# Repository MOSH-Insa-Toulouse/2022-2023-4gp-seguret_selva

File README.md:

# 2022-2023-4gp-seguret_selva
## Notre projet MOSH - julien &amp; clément  
  
Dans le cadre de l'UF "Du capteur au banc de test en Open Source Hardware", nous avons été amenés à réaliser un capteur de déformation low-tech à base de graphite
Le fonctionnement de ce capteur est basé sur la variation de résistance engendrée par la déformation de celui-ci.
La physique derrière cette variation de résistance vient du déplacement des électrons par effet tunnel entre les nanoparticules de graphite.
Après avoir appliqué une contrainte mécanique, la distance entre les nanoparticules varie, entraînant donc une modification de la conductivité du graphite.
Cela induit donc une variation de résistance du capteur.  
  
Voici une image représentant notre capteur low-tech à base de graphite :  

Dans ce fichier nous allons décrire tous les procédés qui ont permis d'aboutir à la création de ce capteur.  
  
Table des matières :  
  
* [1. Cahier des charges](#PremiereSection)  
* [2. Simulation électronique du circuit transimpédance sur LTSpice](#DeuxiemeSection) 
* [3. Le design de notre PCB sur KiCAD](#TroisiemeSection)
* [4. Notre code Arduino](#QuatriemeSection)  
* [5. Notre application Bluetooth](#CinquiemeSection)
* [6. Le banc de test et l'élaboration de la Datasheet](#SixiemeSection)  
    
### *1. Cahier des charges* 
  
Nous sommes en binôme pour réaliser ce projet qui comprend plusieurs différents livrables :  
* Un Shield PCB au préalable designé sur KiCAD  
* Une application Android fonctionnant par Bluetooth permettant de visualiser l'évolution de la résistance du capteur en temps réel  
* Un code Arduino permettant de calculer en temps réel la variation de résistance du capteur ainsi que de contrôler les élements du PCB  
* Une datasheet regroupant les caractéristiques de fonctionnement du capteur  
  
Ainsi, afin de réaliser ce projet, il nous a été nécessaire de réaliser la simulation du capteur sur le logiciel LTSpice pour avoir une idée de l'ordre de grandeur de la résitance de celui-ci. 
Nous avons ensuite utlisé le logiciel KiCAD dans le but de designer le Shield PCB relatif au bon fonctionnement du capteur, et redigé un code Arduino
permettant le contrôle de certains éléments du Shield tels que le Flex Sensor, le module Bluetooth et l'écran OLED. Ce code Arduino nous permet également de calculer 
en temps réel la valeur de la résistance du capteur.
Après avoir effectué tout cela, nous avons créé une application APK Android permettant de connecter le module Bluetooth du PCB au téléphone de Julien, et de
visualiser l'évolution de la résistance du capteur sur un graphique en temps réel.
Enfin, la dernière étape visait à la réalisation d'une datasheet, via la caractérisation de notre jauge de contrainte.  
  
Le matériel suivant a été nécessaire à la confection de notre projet :  
* Une carte Arduino UNO    
* Un module Bluetooth HC-05  
* Un écran OLED I2C  
* Un amplificateur opérationnel LTC1050  
* Deux résistances de 100 KOhms  
* Une résistance de 10 KOhms  
* Deux résistances de 1 KOhm  
* Deux condensateurs de 100 nF  
* Un condensateur de 100 µF  
* Une feuille de papier  
* Cinq crayons à papier différents  
  
### *2. Simulation électronique du circuit transimpédance sur LTSpice*  
  
Comme nous l'avons démontré dans le document nommé [Rapport LTSpice](https://github.com/MOSH-Insa-Toulouse/2022-2023-4gp-seguret_selva/blob/main/LTSpice/Rapport%20LTSpice.pdf), le capteur ne délivrait qu'une intensité très faible (de l'ordre de quelques nF). Aussi, la carte Arduino n'est capable de sortir qu'une tension entre 0 et 5V.  
Ainsi, il nous est apparu comme nécessaire de réaliser un circuit transimpédance afin de convertir les variations de courant du capteur en variations de tension, de sorte
que la carte Arduino puisse la lire en temps réel. En parallèle de tout ça, sur ce circuit, nous avons placé quelques filtres passe-bas nous permettant de réduire les bruits
liés à la mesure, et nous permettant à l'aide d'un amplificateur LTC1050 d'amplifier le signal de sortie.  
  
Voici, la simulation de notre amplificateur transimpédance réalisé sur le logiciel LTSpice :  

### *3. L'utilisation de KiCAD en vue de la création de notre PCB*   
  
Dans l'objectif de réaliser notre PCB, nous avons dû utiliser le logiciel KiCAD. Certains composants n'étant pas disponibles dans les librairies du logiciel, 
nous les avons créés afin de pouvoir designer tous les éléments dont nous avions besoin pour réaliser le Shield. Ce sont les éléments suivants accompagnés
de leur empreinte et de leur schéma :  
  
* Le module Bluetooth HC-05 :  
  
* L'amplificateur opérationnel LTC1050 :   
  
* L'écran OLED I2C :  
  
* Le Flex Sensor :  
   
* Le capteur graphite :  

Vous pouvez également visualiser ici le schéma de notre Shield Arduino ainsi que de la PCB :  

### *4. Notre code Arduino*   
  
Notre code Arduino nous a permis de connecter tous les éléments du Shield entre eux afin d'assurer le bon fonctionnement de celui-ci.  
Rappelons que notre code Arduino que l'on peut retrouver dans le document nommé [AffichageRes](https://github.com/MOSH-Insa-Toulouse/2022-2023-4gp-seguret_selva/blob/main/Code%20Arduino/AffichageRes) prend en charge les fonctionnalités suivantes :  
* L'envoi et la réception de données sur l'application APK via le module Bluetooth HC-05  
* Le calcul en temps réel de la variation de résistance associée à la déformation du capteur graphite  
* L'acquistion et l'affichage de cette valeur de résistance sur l'écran OLED  
* Le lancement de l'acquisition de données pour une certaine valeur de déformation du Flex Sensor  

### *5. Notre application Bluetooth*  
  
Notre application Andoid a été développée à l'aide du logiciel *MIT App Inventor*. Nous avons créé une interface graphique téléchargeable sur Android afin de :  
* Connecter une téléphone au PCB via le module Bluetooth  
* Visualiser en temps réel sous forme de graphique l'évolution de la résistance en fonction de la déformation  
* Afficher la résistance du capteur en temps réel  
  
### *6. Le banc de test et l'élaboration de la Datasheet*   
  
Comme nous avons créé un capteur graphite low-tech, nous avons également décidé d'utiliser un banc de test low-tech.
Le banc de test que vous pouvez voir ci-dessous a été créé il y a quelques années par l'un des professeurs de l'INSA Toulouse.  

Ce banc de test nous a permis de tester différents angles de courbure pour notre capteur. En effet, nous avons placé notre capteur graphite sur les différentes
portions de cette pièce, afin de faire varier sa résistance, que ce soit en tension ou en compression.
  
L’objectif de ce banc de test est de déterminer la variation relative de résistance de notre capteur en fonction de la déformation appliquée. Le capteur graphite est quant à lui scotché par une extrémité sur une autre feuille rigide, et pincé au niveau des pins de l’autre extrémité. L’objectif est de courber la feuille de papier rigide sur laquelle est scotché le capteur, afin que celui-ci adopte la forme des cercles de différents rayons.

L'ensemble de ces tests ont été réalisés pour 5 types de crayons différents. Les résultats et analyses de ceux-ci sont disponibles sur le document suivant nommé :
[Datasheet jauge](https://github.com/MOSH-Insa-Toulouse/2022-2023-4gp-seguret_selva/blob/main/Datasheet/Datasheet%20jauge.pdf)  
  
Il faut noter que notre capteur fonctionne assez bien car, pour n'importe quel type de crayon, la variation relative de résistance de notre capteur en fonction de la 
déformation appliquée est quasi-linéaire.  
  
Malheureusement, il est notable que notre capteur graphite s'endommage assez rapidement lorsque l'on le plie car le papier n'est pas solide. Il n'est donc pas
possible de réaliser la mesure plusieurs fois afin de vérifier ses résultats, ce qui rend la datasheet assez imprécise. Cela se traduit également par le fait que 
les courbes obtenues ne sont pas totalement linéaires. Aussi, le dépôt de graphite lors du coloriage du papier est assez aléatoire, rendant le capteur
encore plus imprécis.  
  
Tous ces éléments nous laissent ainsi penser que ce capteur low-tech est réalisable, mais n'est pas nécessairement très adapté à un usage industriel.

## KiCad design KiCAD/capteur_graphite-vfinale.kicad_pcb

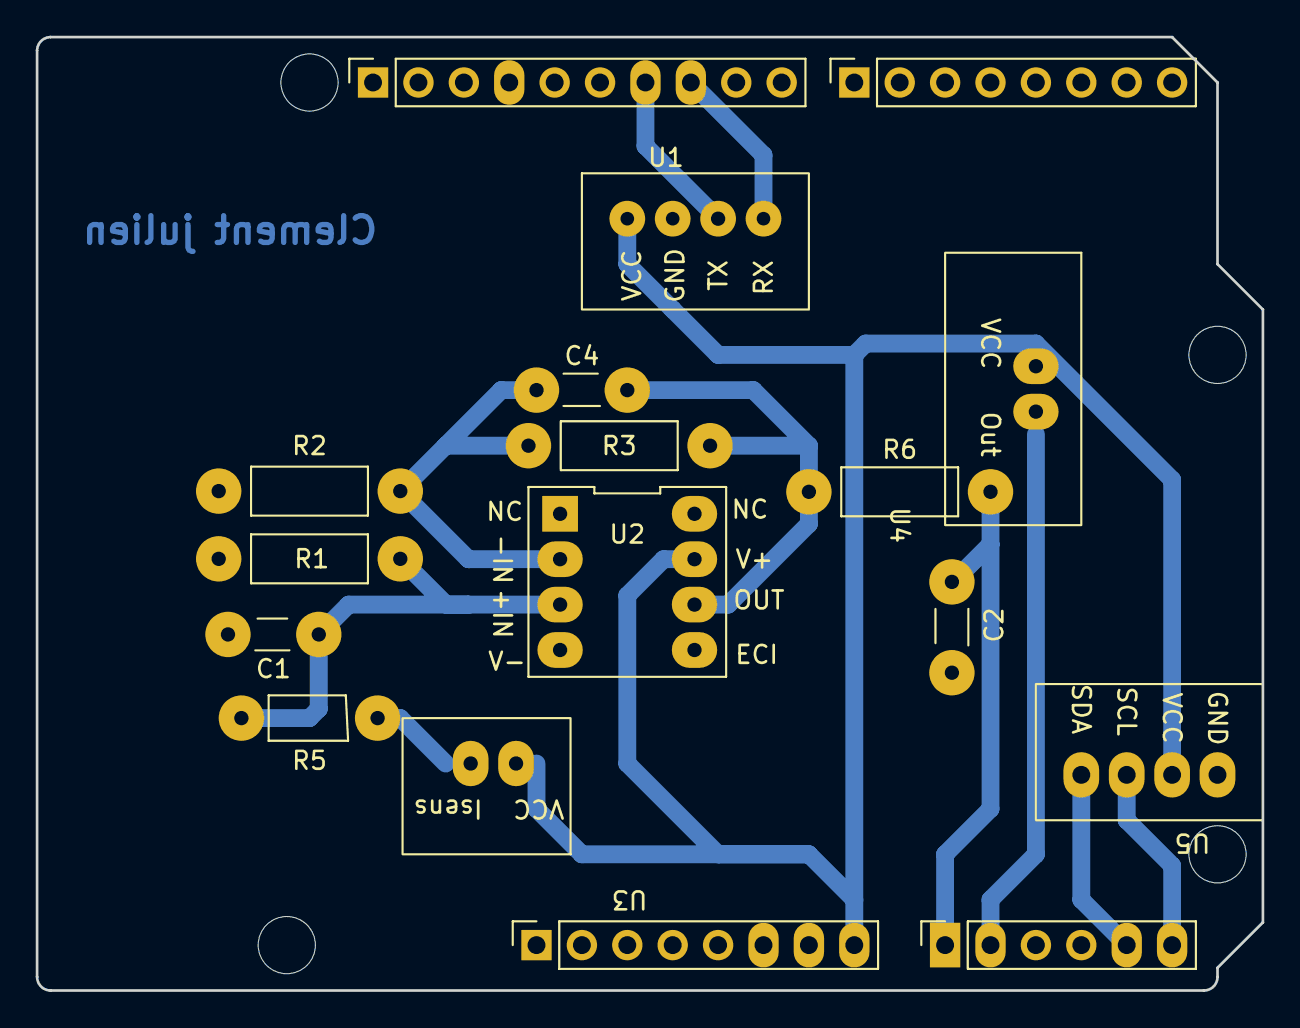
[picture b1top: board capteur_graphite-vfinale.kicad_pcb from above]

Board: 2 copper layers, 68.6 x 53.3 mm, 21 parts (0 on the bottom side), 12 nets.

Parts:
C1, C2: 100n; R_Axial_DIN0204_L3.6mm_D1.6mm_P5.08mm_Horizontal
C4: 1µ; R_Axial_DIN0204_L3.6mm_D1.6mm_P5.08mm_Horizontal
J1: Power; PinSocket_1x08_P2.54mm_Vertical
J2: Digital/PWM; PinSocket_1x10_P2.54mm_Vertical
J3: Analog; PinSocket_1x06_P2.54mm_Vertical
J4: Digital/PWM; PinSocket_1x08_P2.54mm_Vertical
MH1, MH2, MH3, MH4: MountingHole_3.2mm
R1, R3: 100k; R_Axial_DIN0207_L6.3mm_D2.5mm_P10.16mm_Horizontal
R2, R6: 1k; R_Axial_DIN0207_L6.3mm_D2.5mm_P10.16mm_Horizontal
R5: 10k; R_Axial_DIN0207_L6.3mm_D2.5mm_P7.62mm_Horizontal
U1: Modem_BT; BT_empreinte
U2: LTC1050
U3: Graphite_flex_sensor
U4: Spectra_flex_sensor
U5: OLED_screen

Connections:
/*10: J2.8, U1.4 (RX)
/*11: J2.7, U1.3 (TX)
/A0: C2.1, J3.1, R6.2
/A1: J3.2, U4.2 (Out)
/SCL/A5: J2.1, J3.6, U5.3 (SCL)
/SDA/A4: J2.2, J3.5, U5.4 (SDA)
GND: C1.2, C2.2, J1.6, J1.7, J2.4, R1.2, R2.2, U1.2 (GND), U2.4 (V-), U5.1 (GND)
unnamed: C1.1, R1.1, R5.2, U2.3 (+)
unnamed: C4.1, R2.1, R3.1, U2.2 (-)
unnamed: C4.2, R3.2, R6.1, U2.6
unnamed: R5.1, U3.2 (Isens)
VCC: J1.8, U1.1 (VCC), U2.7 (V+), U3.1 (VCC), U4.1 (Vcc), U5.2 (VCC)

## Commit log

2023-05-10 Create AffichageRes
